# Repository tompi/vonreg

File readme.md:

# The Vonreg keyboard
---------------------

The Vonreg is an attempt at exploiting 3 dimensions with just pcb.
(vertical thumb cluster)

N.B: Although this board works fine, its a bit difficult to use,
since it will slide around, due to only 2 edges touching the table.

To build it you need to order pcbs, check out the releases.

You will also need the following parts:
2 x Blackpill MCU
2 x TRRS Jack
36 x MX switches and keycaps
4 x 2.54mm Double Row Right angle Male Breakaway PCB Board Pin Header Connector(2x5 pins)
1 x USB C cable
1 x TRRS cable (only need 3 poles)

Optional:
1 x Buzzer (4mm between pins)

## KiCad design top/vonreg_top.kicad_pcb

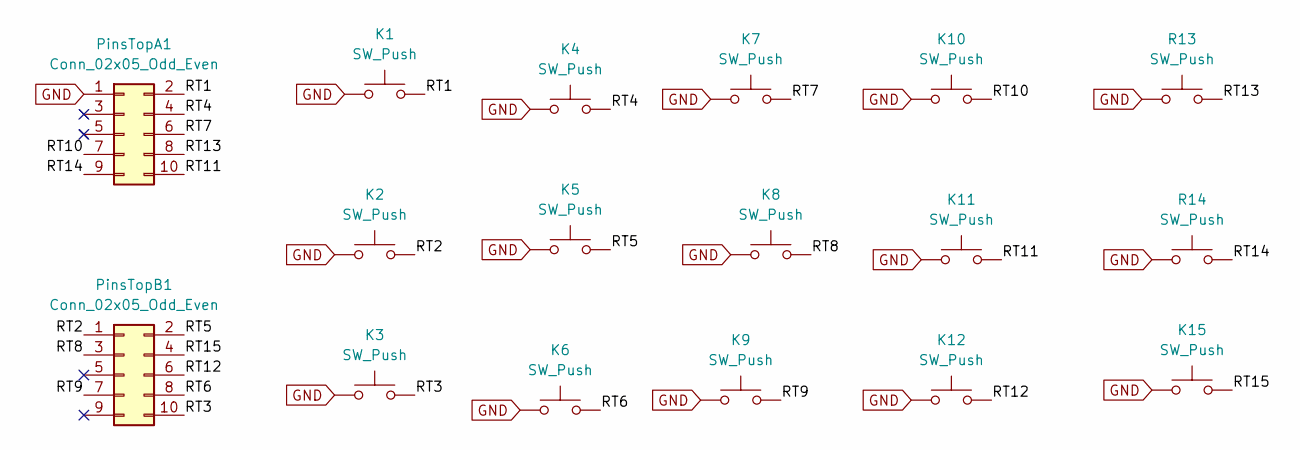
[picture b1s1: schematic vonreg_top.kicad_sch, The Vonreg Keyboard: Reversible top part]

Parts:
K1, K2, K3, K4, K5, K6, K7, K8, K9, K10, K11, K12, K15: SW_Push; Kailh_socket_MX_optional_reversible
PinsTopA1: Conn_02x05_Odd_Even; PinHeader_2x05_P2.54mm_Vertical
PinsTopB1: Conn_02x05_Odd_Even; PinHeader_2x05_P2.54mm_Vertical
R13, R14: SW_Push; Kailh_socket_MX_optional_reversible

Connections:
/RT1: K1.2, PinsTopA1.2
/RT2: K2.2, PinsTopB1.1
/RT3: K3.2, PinsTopB1.10
/RT4: K4.2, PinsTopA1.4
/RT5: K5.2, PinsTopB1.2
/RT6: K6.2, PinsTopB1.8
/RT7: K7.2, PinsTopA1.6
/RT8: K8.2, PinsTopB1.3
/RT9: K9.2, PinsTopB1.7
/RT10: K10.2, PinsTopA1.7
/RT11: K11.2, PinsTopA1.10
/RT12: K12.2, PinsTopB1.6
/RT13: PinsTopA1.8, R13.2
/RT14: PinsTopA1.9, R14.2
/RT15: K15.2, PinsTopB1.4
GND: K1.1, K2.1, K3.1, K4.1, K5.1, K6.1, K7.1, K8.1, K9.1, K10.1, K11.1, K12.1, K15.1, PinsTopA1.1, R13.1, R14.1

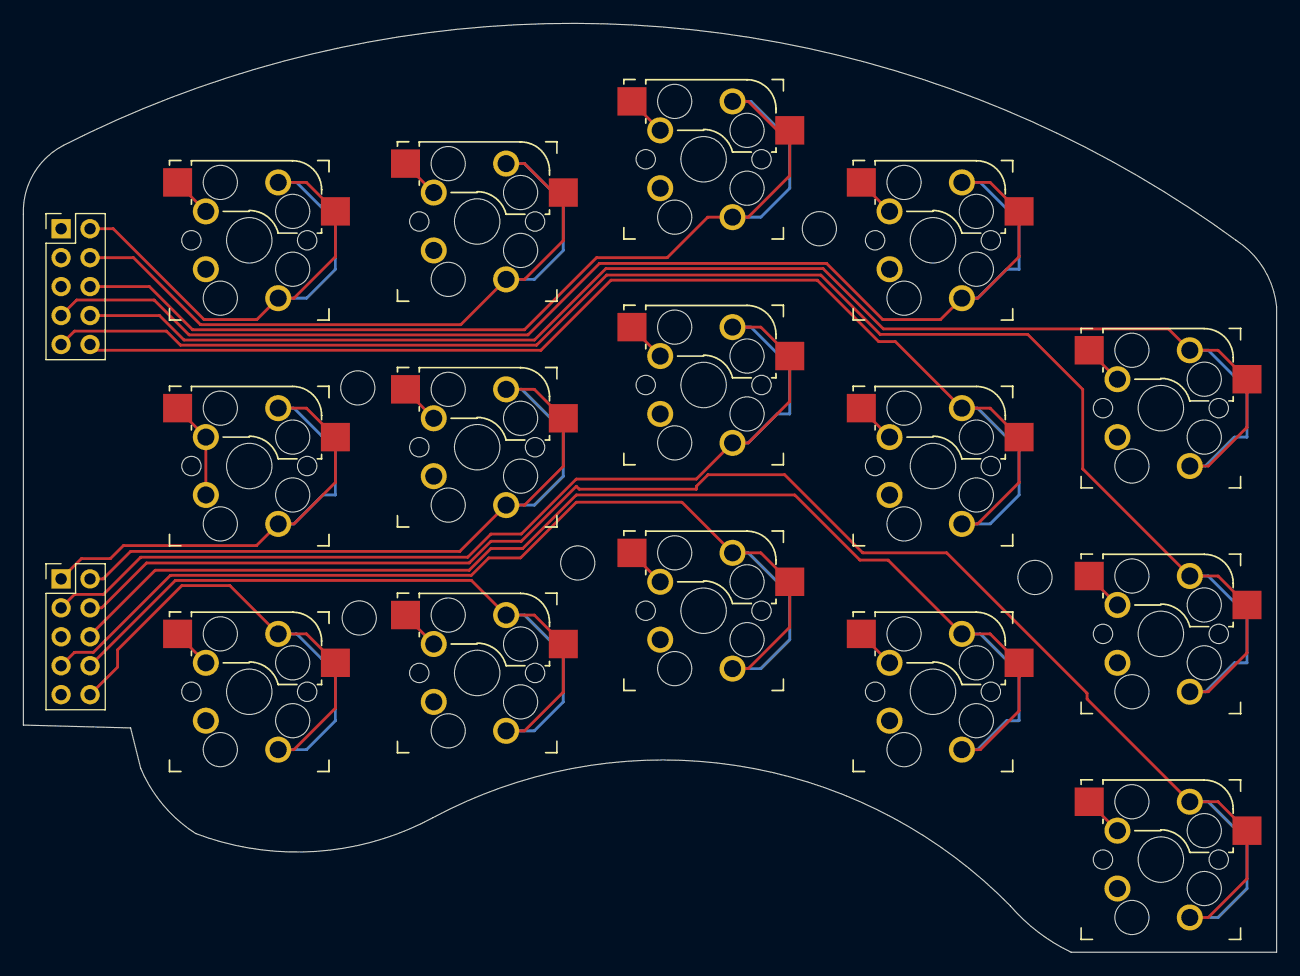
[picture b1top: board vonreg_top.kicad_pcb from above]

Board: 2 copper layers, 110.0 x 81.5 mm, 22 parts (0 on the bottom side), 16 nets.

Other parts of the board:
H1, H1#2, H1#3, H1#4, H1#5: MountingHole_3mm

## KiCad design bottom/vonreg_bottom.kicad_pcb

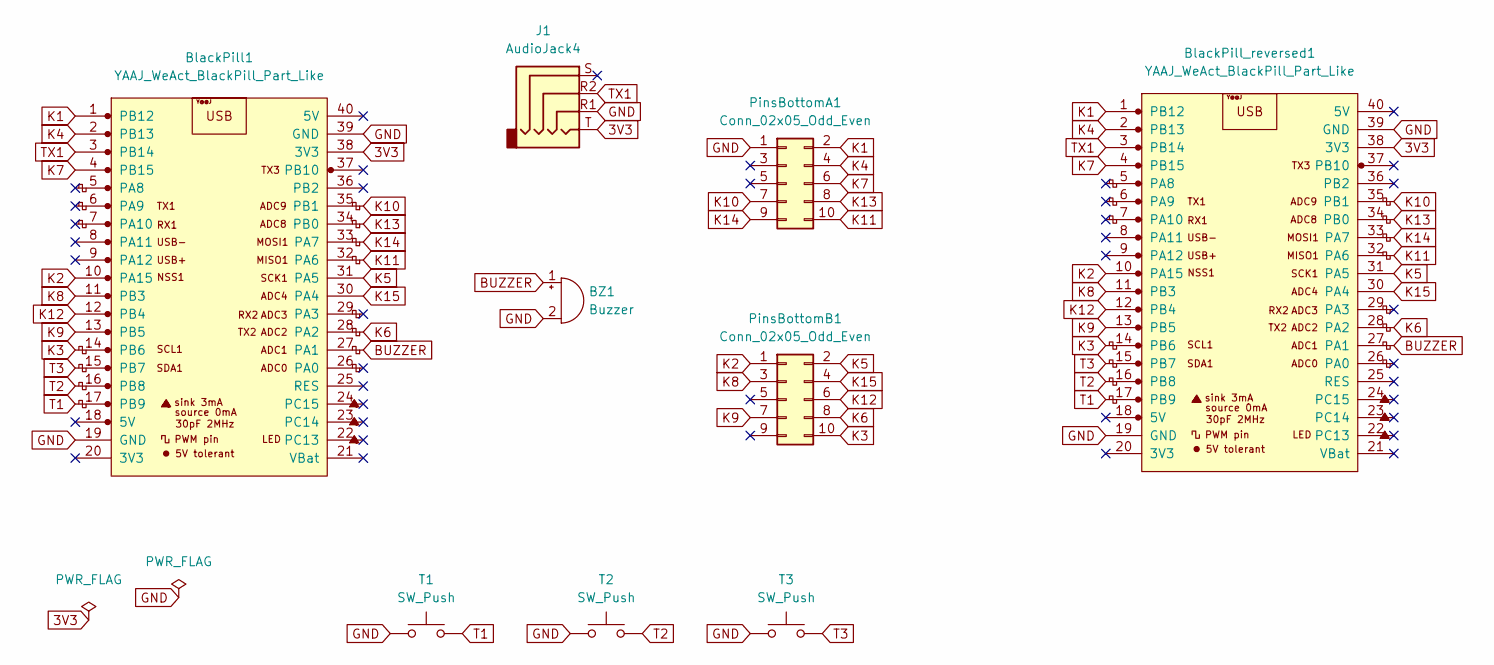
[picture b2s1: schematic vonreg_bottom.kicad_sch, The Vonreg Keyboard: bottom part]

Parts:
BZ1: Buzzer; MagneticBuzzer_PUI_AT-0927-TT-6-R
BlackPill1: YAAJ_WeAct_BlackPill_Part_Like; YAAJ_WeAct_BlackPill_2
BlackPill_reversed1: YAAJ_WeAct_BlackPill_Part_Like; YAAJ_WeAct_BlackPill_2
J1: AudioJack4; TRRS-PJ-320A-dual
PinsBottomA1: Conn_02x05_Odd_Even; PinHeader_2x05_P2.54mm_Vertical
PinsBottomB1: Conn_02x05_Odd_Even; PinHeader_2x05_P2.54mm_Vertical
T1, T2, T3: SW_Push; Kailh_socket_MX_optional_reversible

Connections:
3V3: BlackPill1.38 (3V3), BlackPill_reversed1.38 (3V3), J1.T
BUZZER: BZ1.1 (-), BlackPill1.27 (PA1), BlackPill_reversed1.27 (PA1)
GND: BZ1.2 (+), BlackPill1.19 (GND), BlackPill1.39 (GND), BlackPill_reversed1.19 (GND), BlackPill_reversed1.39 (GND), J1.R1, PinsBottomA1.1, T1.1, T2.1, T3.1
K1: BlackPill1.1 (PB12), BlackPill_reversed1.1 (PB12), PinsBottomA1.2
K2: BlackPill1.10 (PA15), BlackPill_reversed1.10 (PA15), PinsBottomB1.1
K3: BlackPill1.14 (PB6), BlackPill_reversed1.14 (PB6), PinsBottomB1.10
K4: BlackPill1.2 (PB13), BlackPill_reversed1.2 (PB13), PinsBottomA1.4
K5: BlackPill1.31 (PA5), BlackPill_reversed1.31 (PA5), PinsBottomB1.2
K6: BlackPill1.28 (PA2), BlackPill_reversed1.28 (PA2), PinsBottomB1.8
K7: BlackPill1.4 (PB15), BlackPill_reversed1.4 (PB15), PinsBottomA1.6
K8: BlackPill1.11 (PB3), BlackPill_reversed1.11 (PB3), PinsBottomB1.3
K9: BlackPill1.13 (PB5), BlackPill_reversed1.13 (PB5), PinsBottomB1.7
K10: BlackPill1.35 (PB1), BlackPill_reversed1.35 (PB1), PinsBottomA1.7
K11: BlackPill1.32 (PA6), BlackPill_reversed1.32 (PA6), PinsBottomA1.10
K12: BlackPill1.12 (PB4), BlackPill_reversed1.12 (PB4), PinsBottomB1.6
K13: BlackPill1.34 (PB0), BlackPill_reversed1.34 (PB0), PinsBottomA1.8
K14: BlackPill1.33 (PA7), BlackPill_reversed1.33 (PA7), PinsBottomA1.9
K15: BlackPill1.30 (PA4), BlackPill_reversed1.30 (PA4), PinsBottomB1.4
T1: BlackPill1.17 (PB9), BlackPill_reversed1.17 (PB9), T1.2
T2: BlackPill1.16 (PB8), BlackPill_reversed1.16 (PB8), T2.2
T3: BlackPill1.15 (PB7), BlackPill_reversed1.15 (PB7), T3.2
TX1: BlackPill1.3 (PB14), BlackPill_reversed1.3 (PB14), J1.R2

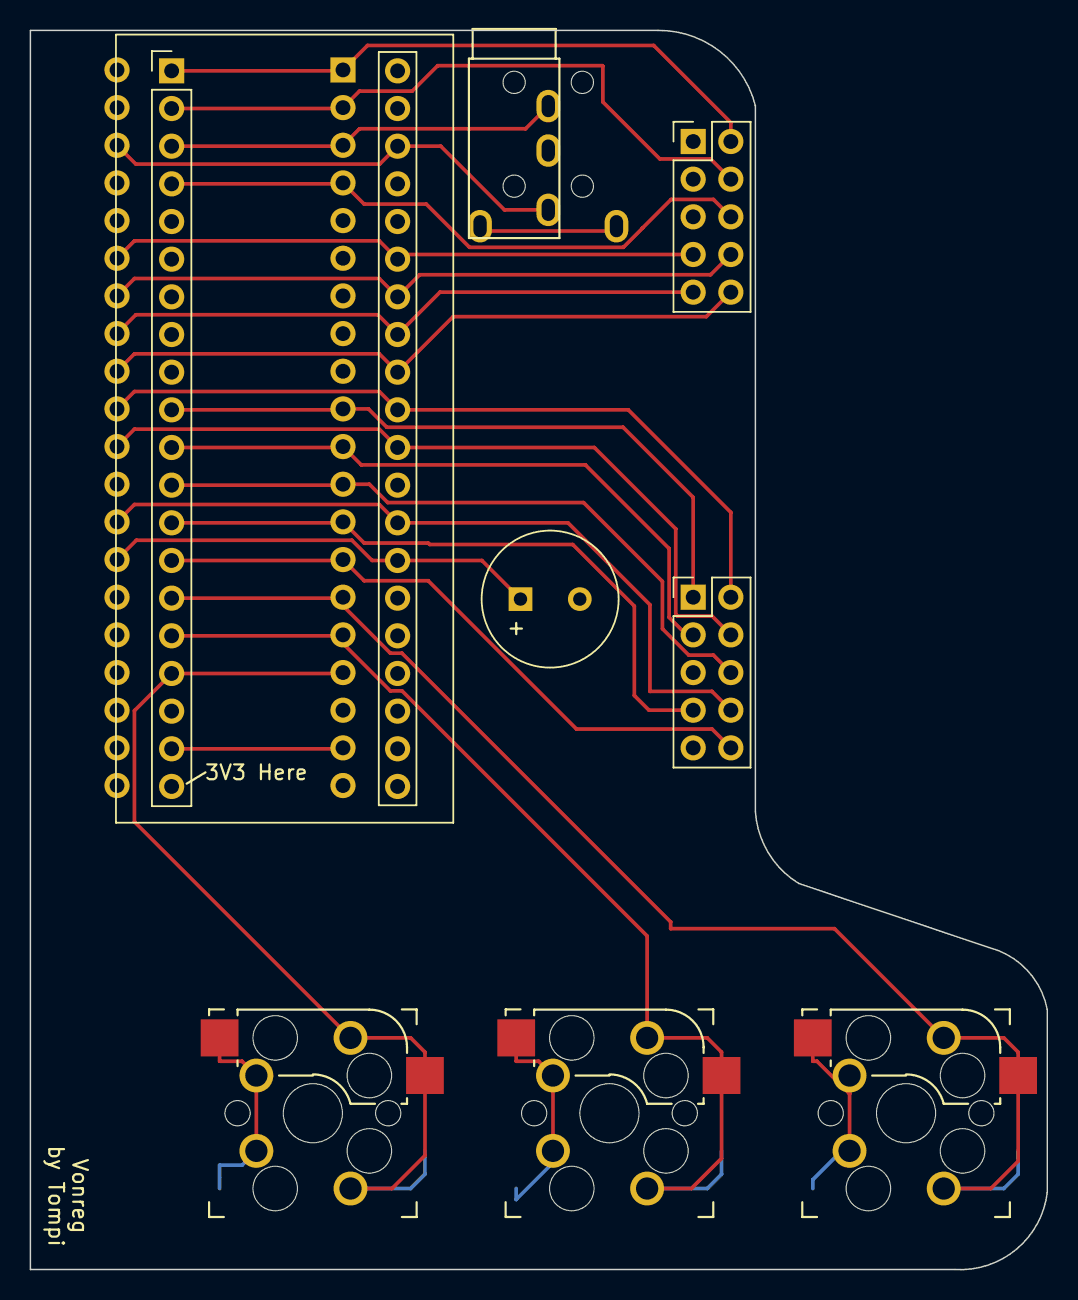
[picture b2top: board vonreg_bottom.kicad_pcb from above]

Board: 2 copper layers, 68.6 x 83.6 mm, 9 parts (1 on the bottom side), 22 nets.

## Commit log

2022-03-07 Bottom passes ERC
2022-03-09 Aligned top/bottom
2022-03-12 Routing done, hopefully
2022-03-12 Rounded edge cuts
2022-03-19 Ground pour and buzzer
2022-03-19 V1 ordered PCB
2022-03-19 Added readme
2022-04-09 top plate: increase margins
2024-06-18 Add picture and warning
